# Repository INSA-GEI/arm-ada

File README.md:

# arm-ada
Repository for 1st generation of INSA handled device used in ADA teaching

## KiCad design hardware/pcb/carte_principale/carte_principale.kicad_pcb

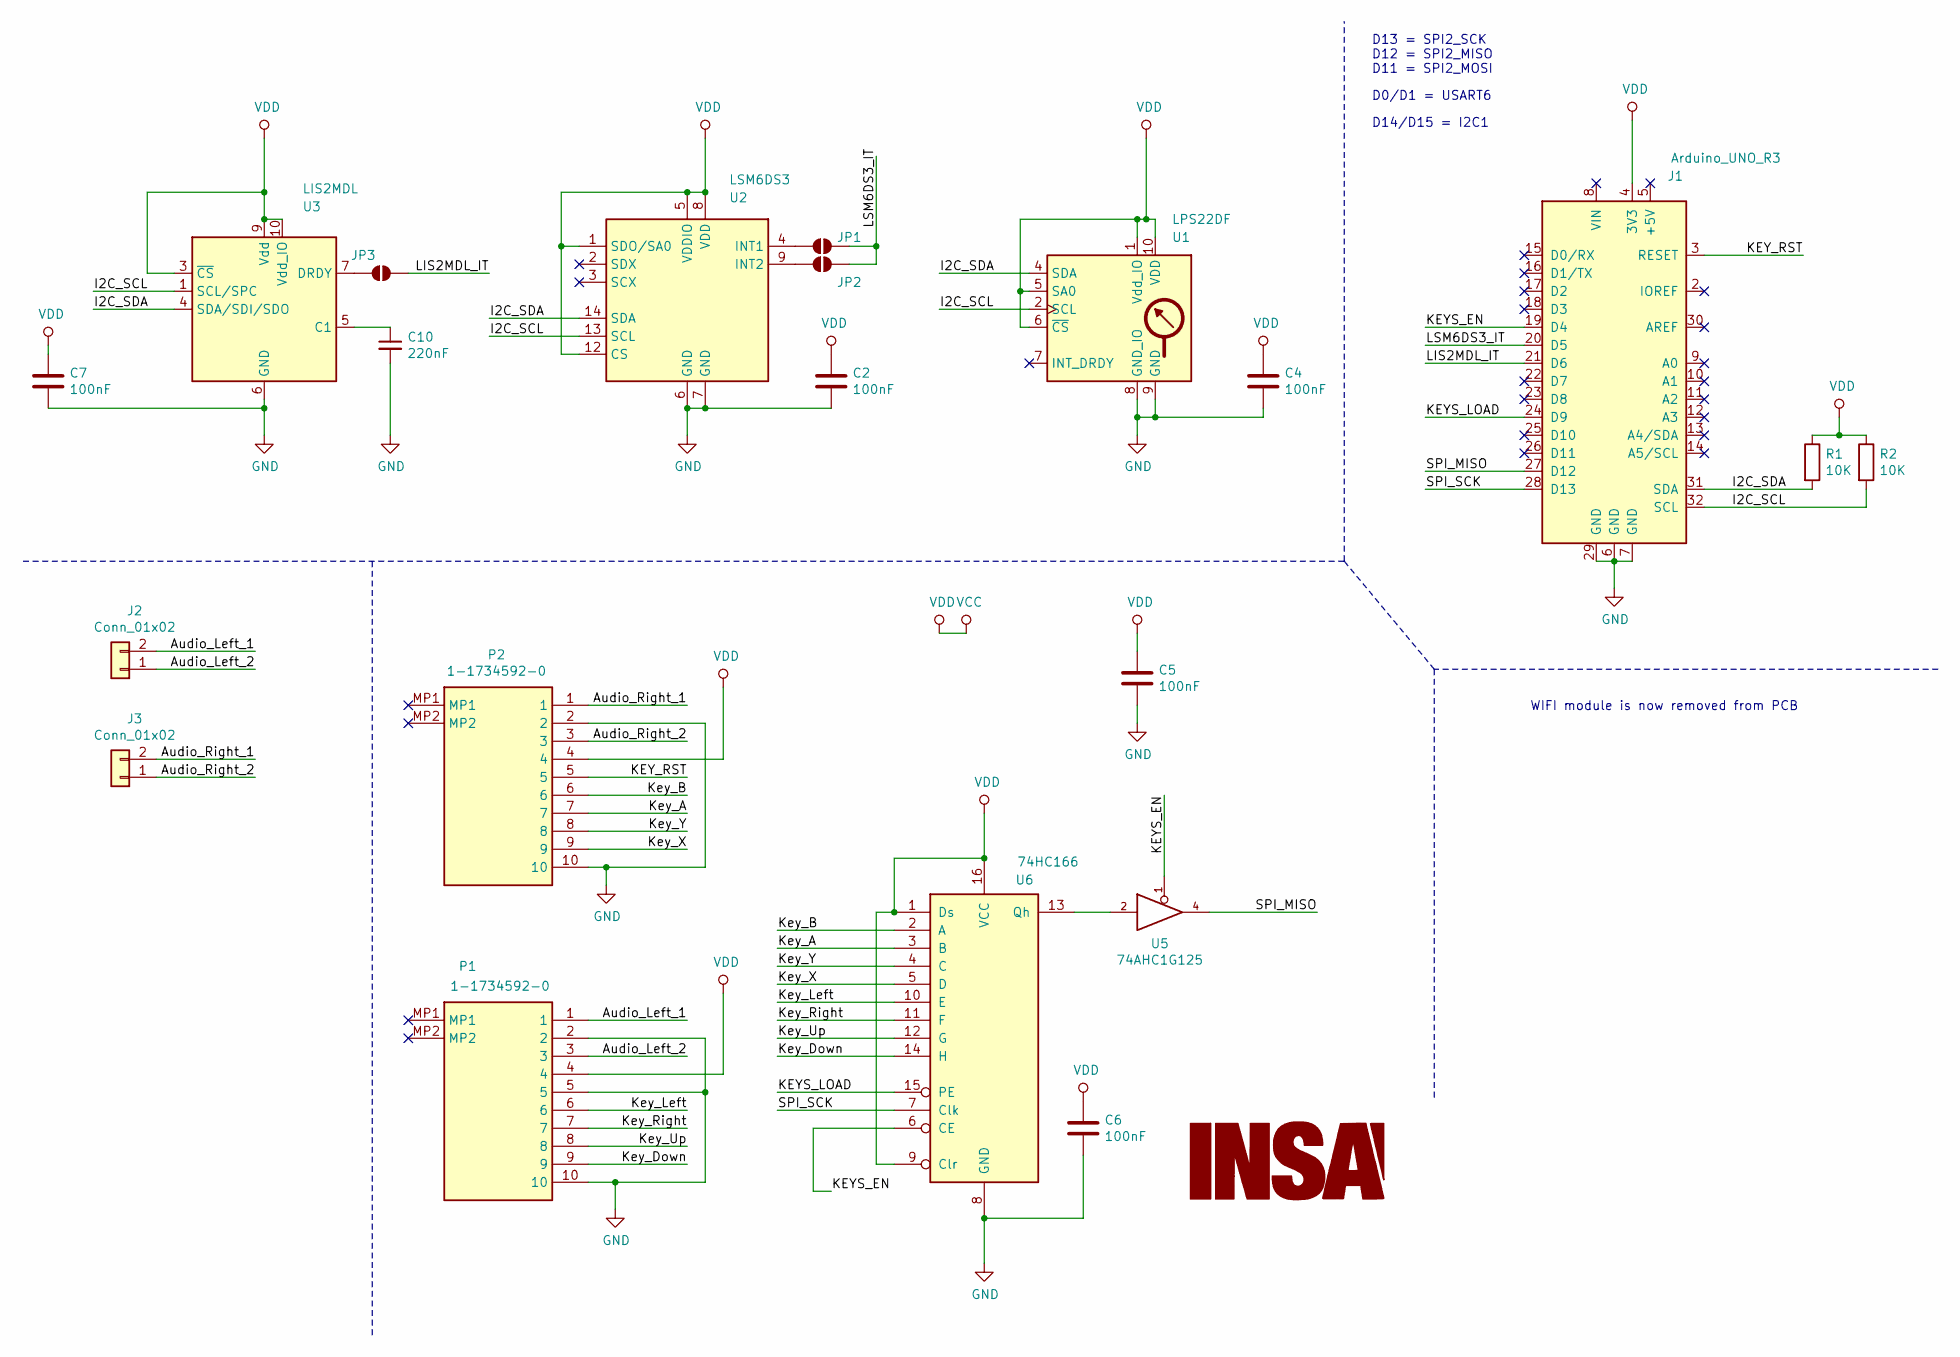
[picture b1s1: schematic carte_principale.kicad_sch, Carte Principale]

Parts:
C2, C4, C5, C6, C7: 100nF; C_1206_3216Metric
C10: 220nF; C_1206_3216Metric
J1: Arduino_UNO_R3; Arduino_UNO_R3_Pin_Only
J2, J3: Conn_01x02; PinHeader_1x02_P2.54mm_Vertical
JP1, JP2, JP3: SJ; SolderJumper-2_P1.3mm_Open_RoundedPad1.0x1.5mm
Logo1: LOGO; insa-image
P1, P2: 1-1734592-0; 117345920; Mouser Part Number 571-1-1734592-0
R1, R2: 10K; R_1206_3216Metric
U1: LPS22DF; ST_HLGA-10_2x2mm_P0.5mm_LayoutBorder3x2y
U2: LSM6DS3; LGA-14_3x2.5mm_P0.5mm_LayoutBorder3x4y-slim
U3: LIS2MDL; LGA-12_2x2mm_P0.5mm
U5: 74AHC1G125; SOT-353_SC-70-5
U6: 74HC166; SOIC-16_3.9x9.9mm_P1.27mm

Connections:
/Audio_Left_1: J2.2, P1.1
/Audio_Left_2: J2.1, P1.3
/Audio_Right_1: J3.2, P2.1
/Audio_Right_2: J3.1, P2.3
/I2C_SCL: J1.32 (SCL), R2.2, U1.2 (SCL), U2.13 (SCL), U3.1 (SCL/SPC)
/I2C_SDA: J1.31 (SDA), R1.2, U1.4 (SDA), U2.14 (SDA), U3.4 (SDA/SDI/SDO)
/KEYS_EN: J1.19 (D4), U5.1, U6.6 (CE)
/KEYS_LOAD: J1.24 (D9), U6.15 (PE)
/KEY_RST: J1.3 (RESET), P2.5
/Key_A: P2.7, U6.3 (B)
/Key_B: P2.6, U6.2 (A)
/Key_Down: P1.9, U6.14 (H)
/Key_Left: P1.6, U6.10 (E)
/Key_Right: P1.7, U6.11 (F)
/Key_Up: P1.8, U6.12 (G)
/Key_X: P2.9, U6.5 (D)
/Key_Y: P2.8, U6.4 (C)
/LIS2MDL_IT: J1.21 (D6), JP3.1 (A)
/LSM6DS3_IT: J1.20 (D5), JP1.2 (B), JP2.2 (B)
/SPI_MISO: J1.27 (D12), U5.4
/SPI_SCK: J1.28 (D13), U6.7 (Clk)
GND: C2.2, C4.2, C5.2, C6.2, C7.2, C10.2, J1.6 (GND), J1.7 (GND), J1.29 (GND), P1.2, P1.5, P1.10, P2.2, P2.10, U1.3 (GND), U1.8 (GND_IO), U1.9 (GND), U2.6 (GND), U2.7 (GND), U3.6 (GND), U3.8 (GND), U5.3 (GND), U6.8 (GND)
unnamed: JP1.1 (A), U2.4 (INT1)
unnamed: JP2.1 (A), U2.9 (INT2)
unnamed: JP3.2 (B), U3.7 (DRDY)
unnamed: C10.1, U3.5 (C1)
unnamed: U5.2, U6.13 (Qh)
VCC: C2.1, C4.1, C5.1, C6.1, C7.1, J1.4 (3V3), P1.4, P2.4, R1.1, R2.1, U1.1 (Vdd_IO), U1.5 (SA0), U1.6 (~CS), U1.10 (VDD), U2.1 (SDO/SA0), U2.5 (VDDIO), U2.8 (VDD), U2.12 (CS), U3.3 (~CS), U3.9 (Vdd), U3.10 (Vdd_IO), U5.5 (VCC), U6.1 (Ds), U6.9 (Clr), U6.16 (VCC)

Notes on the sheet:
D13 = SPI2_SCK D12 = SPI2_MISO D11 = SPI2_MOSI
D0/D1 = USART6
WIFI module is now removed from PCB
D14/D15 = I2C1

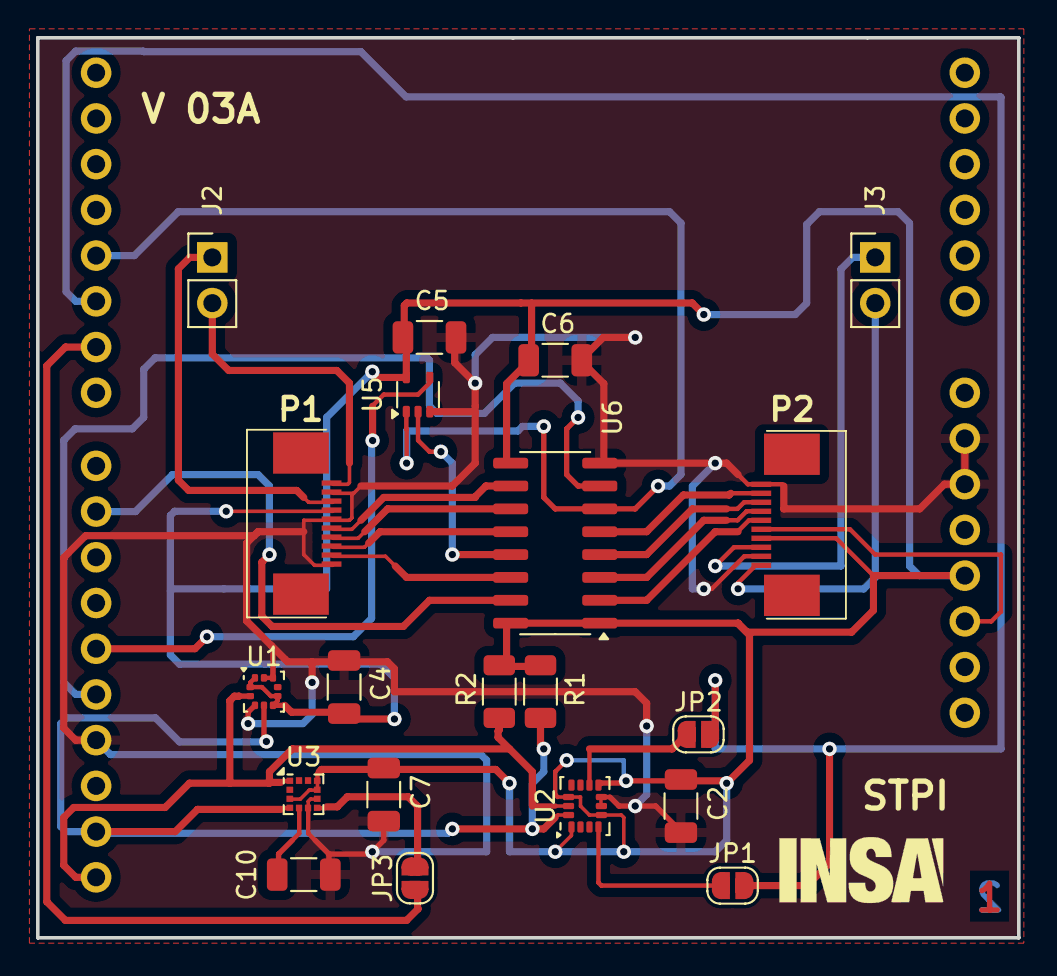
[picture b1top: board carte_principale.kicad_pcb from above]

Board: 2 copper layers, 54.5 x 50.0 mm, 22 parts (1 on the bottom side), 28 nets.

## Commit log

2019-02-19 initial release, from sourcesup
2019-03-15 Modification du TP2 Simon
2019-03-25 correction du simon
2019-07-16 Ajout du debuger sous vscode
2019-07-17 modifications pour supporter les gameboy de nouvelle generation
2020-01-06 version 2.11 avec support des sondes ST-LINK
2021-02-11 simulateur premier jet
2021-02-12 commit avant changement de branche
2021-02-16 avancement sur le simulateur
2021-02-16 Correction sur la taille des boutons
2021-02-17 dialog box fonctionnelles
2021-02-18 Ajout de tests pour l'ecran
2021-02-18 demarrage des fonctions liées aux images
2021-03-01 tests ecran completé
2021-03-02 demarrage du portage de la lib ada INSA pour le simulateur
2021-03-03 Portage de la lib-ada pour le simulateur
2021-03-05 Premier essai du simulateur avec matrix rain
2021-03-09 pacman fonctionne
2021-03-10 simon presque OK, Koch Ok
2021-03-23 gestion de l'IMU et des potar en cours
2021-03-24 Ajout de la commande reset dans le simulateur, support des potentiometres et de l'IMU dans la lib ADA Insa
2021-03-25 simulateur presque fonctionnel à 100%, lib ada idem, reste a travailler sur les makefile
2021-03-25 Petite correction autour du thread d'execution de l'appli ada
2021-03-26 initial commit sur master, correspondant au l'utilisation de gnatstudio et du profil zfs
2021-03-26 commit version 2.13 de la branche legacy du firmware v2
2021-03-29 Import du depot de la console v1
2021-03-29 rajout des fichiers de conception hardware
2021-03-29 importation du simulateur, projet a reprendre
2021-03-31 TP reformatés, simulateur OK mais firmware V2 et TP pour V2 HS
2021-04-07 Version du firmware qui compile avec stm32studio 1.4
2021-04-07 Correction de zone flash qui se superposaient sur le gen2 reste a corriger un bug sur le synthé qui bloque simon et un pb sur le generateur de nombre aleatoire sur snake
2021-04-12 correction du firmware v2 + reorganisation des bibliotheques lib-ada + corrections des makefiles des TP
2021-04-12 Correction sur wrapper v1 + deplacement du firmware v2 dans v2
2021-04-12 rappatriement du firmware de la v1
2021-05-10 importation de la lib ravenscar
2021-05-10 Revert "initial commit sur master, correspondant au l'utilisation de gnatstudio et du profil zfs"
    This reverts commit d64809cde536ec6509b376dd55e68fa29abc776e.
2021-05-10 modification de gitignore
2021-05-10 remodif de .gitignore
2021-05-10 premier step: la bibliotheque ravenscar compile et link avec un projet
2021-05-10 reimport du repertoire "tools" perdu
2021-05-19 Ravenscar commence à fonctionner mais pb de usagefault lors d'une exception => pb avec allocation memoire (sbrk) ?
2021-06-11 Bibliotheque ravenscar full qui semble marcher
2021-06-16 ajout de lvgl
2021-06-17 Integration de lvgl Ok, affichage d'un label en fin d'init BSP: OK
2021-06-23 Nettoyage + ajout d'un projet cubeIDE pour le debug de la BSP
2021-06-23 ajout d'un wrapper ui
2021-06-28 mise en palce des autotests
2021-07-07 corrections sur les fichiers de demarrage et linkerscript => le projet marche sous cubeIDE
2021-07-08 Framework ravenscar-full-armada fonctionne avec lvgl
2021-07-09 Modif lié à l'allocation memoire entre cubeIDE et gnat
2021-07-23 Gestion des fautes et exception ok
2021-09-06 ajout de fichiers support pour les pcb
2021-10-13 Runtime assez stable, lib insa presque complete (manque le son)
2021-10-15 TP pacman porté, TP simon en cours
2021-10-18 TP2 (simon) fonctionne
2021-10-19 Mise a jour des templates de TP + deplacement des bibliotheques support de TP dans /mnt/commetud/2eme année imacs/ADA/lib/lib_TP
2021-10-19 script tools updated
2021-10-22 Tp3.2(Koch) fini + TP4.1(Sensors) + Augmentation stack à 8Ko + Appel de panic dans les exceptions handlers de vectortables.c (runtime ADA) + Ajout des canvas dans lib INSA
2021-10-22 Demarrage conversion snake
2021-11-03 TP4.2 snake OK
2021-11-03 TP3.1 (Dicho) OK
2021-11-03 Ajout de commentaires + remise en forme des fichiers
2021-11-03 ajout et correction des templates de TP
2021-11-17 Ajout des sprites dans le suivi git
2021-11-17 nettoyage du depot avant merge
2021-11-17 Suppression de adainsa.lexch
2021-11-17 Le microphone marche, mais l'affichage des panic et la gestion de la double stack dans le projet de test cubeIDE ne marchent plus
2021-11-19 Changement de niveau de priorité des IT + reduction de l'echantillonage microphone + corrections diverses
2021-11-22 Ajout d'un script python pour gnatstudio + misea à jour fichier gpr
2021-11-24 reference des chemins mis à jour
2021-11-24 creation d'un script d'install
2021-11-24 Correction dans le chemin de ST-LINK_gdbserver.sh
2021-11-25 coorection de script après test sur machine GEI
2021-11-30 Amelioration du script d'installation, ajout du support des solutions dans le script menu_armada
2022-01-11 Mise à jour de arm-ada-setup: recopie des templates de TP dans TPADA2IMACS
2022-03-14 ajout du TP Mission morse
2022-03-16 TP Morse fonctionnel, reste a rajouter le son
2022-03-16 TP Morse complet avec son
2022-03-18 Correction sur projet mission-snake + correction timing symbole sur mission_morse + ajout mission_morse dans fichier de livraison install.py
2022-03-28 Ajout d'un script pour mettre à jour les TP4.1 et TP4.2
2022-04-04 modifications mineures (sur TP4.2)
2023-01-09 Migration de la lib ravenscar en version 2021 + correction dans arm-ada-setup
2023-01-23 Modification du nommage des directions dans les TP pacman (TP1) et snake (TP4.1)
2023-02-06 Correction dans script arm-ada-setup
2023-02-06 suppression des fichiers de la lib ada avant merge de la branche
2024-09-12 commit avant nouveau developpement
2025-04-03 Correction de l'orientation de snake (TP4.1)
2025-04-03 Refresh de la carte capteur
2025-04-24 Ajout du support des nouveaux capteurs. Correction d'un bug d'affichage dans les tests des capteurs. Gros travail de factorisation (bus i2c) et de mise a niveau des drivers mems
2025-04-25 correction du bug de lenteur au demarrage: changement du timing de i2c1 (passage à 1000Khz, mais config possible à 400 Khz)
2025-07-10 Version 3.4: ajout du support de nouveaux capteurs, acceleration du demarrage (I2C à 1000 Khz) et passage des projets à un support 100% complet de /mnt/commetud
2025-10-08 Wip prepaation de la version 3.5, avec nouvelle runtime
2025-10-09 wip 3.5
2025-10-10 WIP changement nom icones pour adaptation au theme + modification script d'installation des TP et autres modifs mineures
2025-10-15 Modification du TP4.1 pour supprimer le tableau des cerise. Commentaire à reprendre
2026-02-05 corrections du reboot automatique dans a-elchha.adb + changement de version de la runtime (3.6) + creationd 'un projet de test (debug_project), a reprendre.
2026-02-06 Petite refactor du code d'affichage des exception (a-elchha.adb) et correction d'un bug (timeout) dans pacman (mission_pacman.adb)
2026-02-06 Reprise du projet tests_runtime
2026-02-09 Modification du volume sonore à morse et ajout du son a simon
